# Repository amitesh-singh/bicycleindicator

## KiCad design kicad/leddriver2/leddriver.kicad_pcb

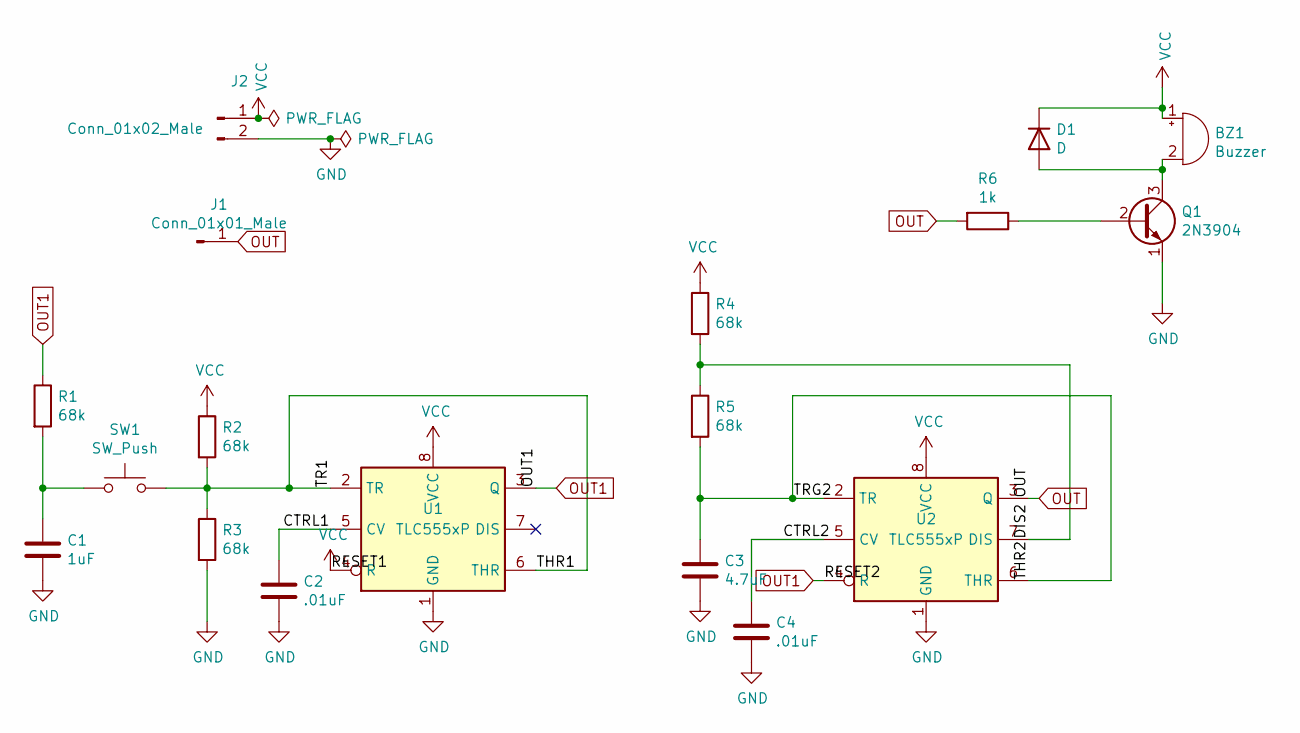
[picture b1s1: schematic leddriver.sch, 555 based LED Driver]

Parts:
BZ1: Buzzer; MagneticBuzzer_ProSignal_ABI-010-RC
C1: 1uF; C_Radial_D8.0mm_H7.0mm_P3.50mm
C2, C4: .01uF; C_Radial_D8.0mm_H7.0mm_P3.50mm
C3: 4.7uF; C_Radial_D8.0mm_H7.0mm_P3.50mm
D1: D; D_5KPW_P7.62mm_Vertical_AnodeUp
J1: Conn_01x01_Male; PinHeader_1x01_P2.54mm_Vertical
J2: Conn_01x02_Male; PinSocket_1x02_P2.54mm_Vertical
Q1: 2N3904; TO-92_HandSolder_Large_Pad
R1, R2, R3, R4, R5: 68k; R_Axial_DIN0204_L3.6mm_D1.6mm_P5.08mm_Horizontal
R6: 1k; R_Axial_DIN0204_L3.6mm_D1.6mm_P5.08mm_Horizontal
SW1: SW_Push; SW_PUSH_6mm_H5mm
U1, U2: TLC555xP; DIP-8_W7.62mm

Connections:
/CTRL1: C2.1, U1.5 (CV)
/CTRL2: C4.1, U2.5 (CV)
/DIS2: R4.2, R5.1, U2.7 (DIS)
/THR1: R2.2, R3.1, SW1.2, U1.2 (TR), U1.6 (THR)
/THR2: C3.1, R5.2, U2.2 (TR), U2.6 (THR)
GND: C1.2, C2.2, C3.2, C4.2, J2.2, Q1.1 (E), R3.2, U1.1 (GND), U2.1 (GND)
unnamed: BZ1.2 (+), D1.2 (A), Q1.3 (C)
unnamed: C1.1, R1.2, SW1.1
unnamed: Q1.2 (B), R6.1
OUT: J1.1, R6.2, U2.3 (Q)
OUT1: R1.1, U1.3 (Q), U2.4 (R)
VCC: BZ1.1 (-), D1.1 (K), J2.1, R2.1, R4.1, U1.4 (R), U1.8 (VCC), U2.8 (VCC)

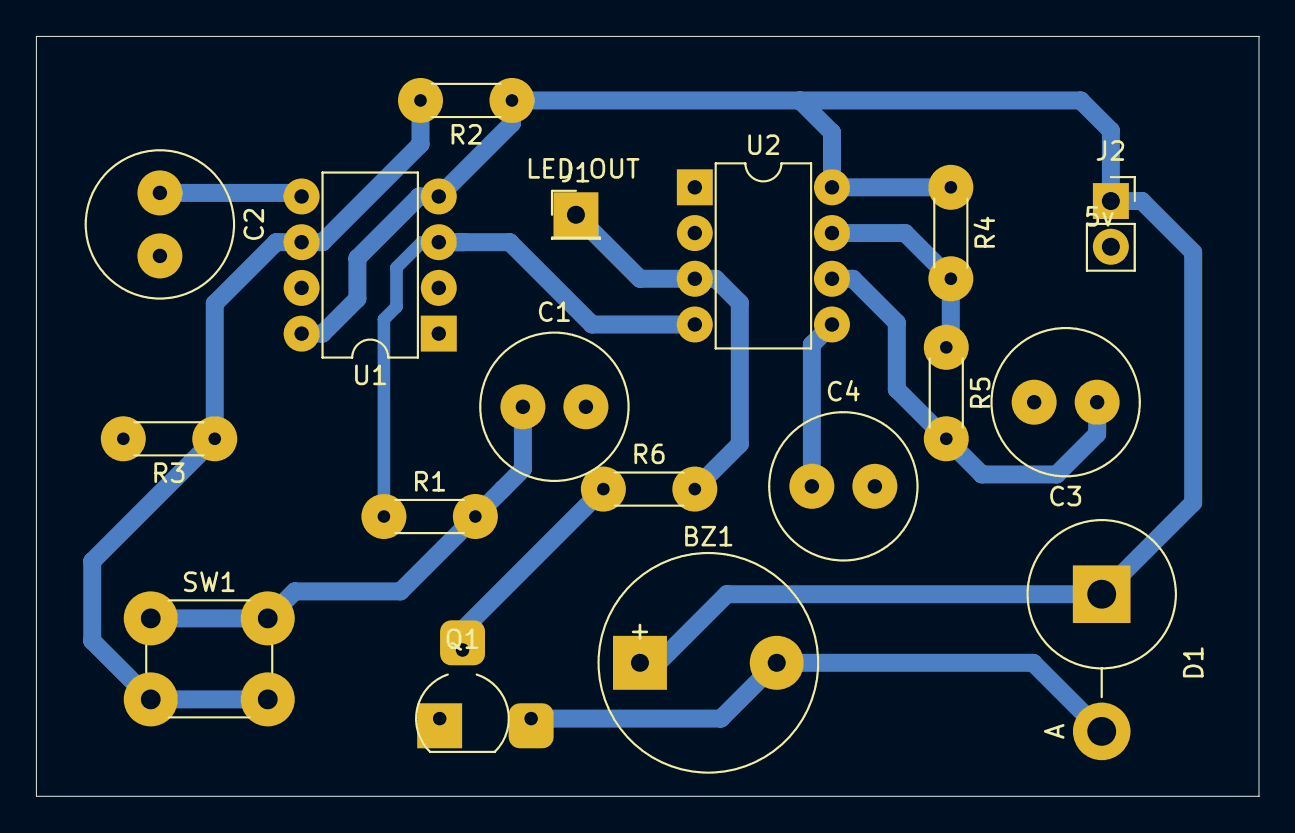
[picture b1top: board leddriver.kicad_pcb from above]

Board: 2 copper layers, 67.9 x 42.2 mm, 18 parts (0 on the bottom side), 12 nets.

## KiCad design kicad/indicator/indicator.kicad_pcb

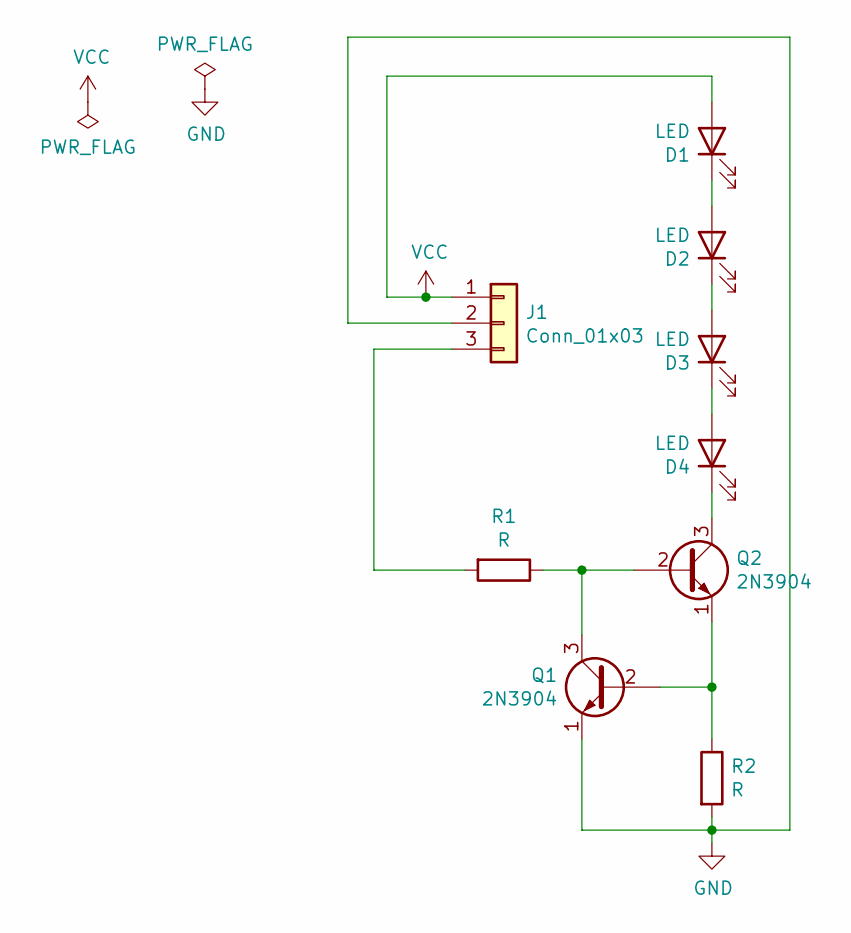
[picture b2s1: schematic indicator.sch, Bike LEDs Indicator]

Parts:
D1, D2, D3, D4: LED; LED_D3.0mm
J1: Conn_01x03; PinSocket_1x03_P2.54mm_Vertical
Q1, Q2: 2N3904; TO-92_Inline
R1, R2: R; R_0805_2012Metric_Pad1.20x1.40mm_HandSolder

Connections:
GND: J1.2, Q1.1 (E), R2.2
unnamed: D1.1 (K), D2.2 (A)
unnamed: D2.1 (K), D3.2 (A)
unnamed: D3.1 (K), D4.2 (A)
unnamed: D4.1 (K), Q2.3 (C)
unnamed: J1.3, R1.2
unnamed: Q1.2 (B), Q2.1 (E), R2.1
unnamed: Q1.3 (C), Q2.2 (B), R1.1
VCC: D1.2 (A), J1.1

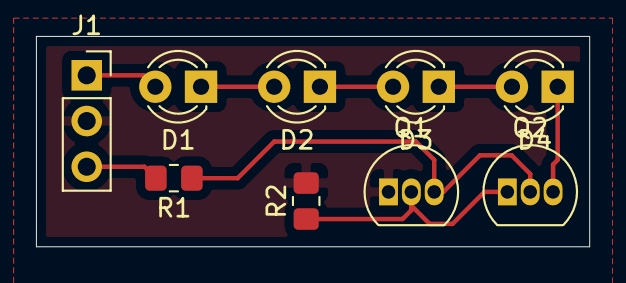
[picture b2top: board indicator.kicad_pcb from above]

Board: 2 copper layers, 30.7 x 11.7 mm, 9 parts (0 on the bottom side), 9 nets.

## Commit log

2017-06-25 Add bicycle indicator firmware code
2017-06-25 Add gitignore
2017-06-25 firmware: make it more C like code by renaming functions name
2017-06-25 Add README.md
    and TODOs.md
2017-06-25 use PCINT1 and 2 for switches
    and PCINT0 for speaker
2017-06-25 works well
2017-06-25 enable timer0 only. disable rest
2017-06-25 comment out unused function
2017-06-26 run at 2x higher speed
2017-06-27 make code compatible at 4.8 MHz
2017-06-27 better to add hardware debounce at switches
2020-10-01 Add initial work for leds indicator work
2020-10-02 add pcb
2020-10-03 update a PCB a bit
2020-10-04 exclude pcb edge disabled.
2020-10-06 Add updated design
    should work with the drill i've
2020-10-10 add footprint for bjts
2020-10-15 Add resistors values
2020-10-17 save ltspice simulation
2020-10-17 save led driver work till now
2020-10-21 Add new code
2020-10-22 Add new led driver schematic
2020-10-24 Add change according to 12v test
2020-10-25 improve the current consumption at standby
    20mA to 10mA now
2020-10-25 update according to new findings on breadboard.
2020-10-25 chnage the schematic
2020-10-28 Add bigger pads and track
2020-10-29 Add new led driver
2020-11-04 Add home etchable version of CC LED
2020-11-16 Add t13a schematic
